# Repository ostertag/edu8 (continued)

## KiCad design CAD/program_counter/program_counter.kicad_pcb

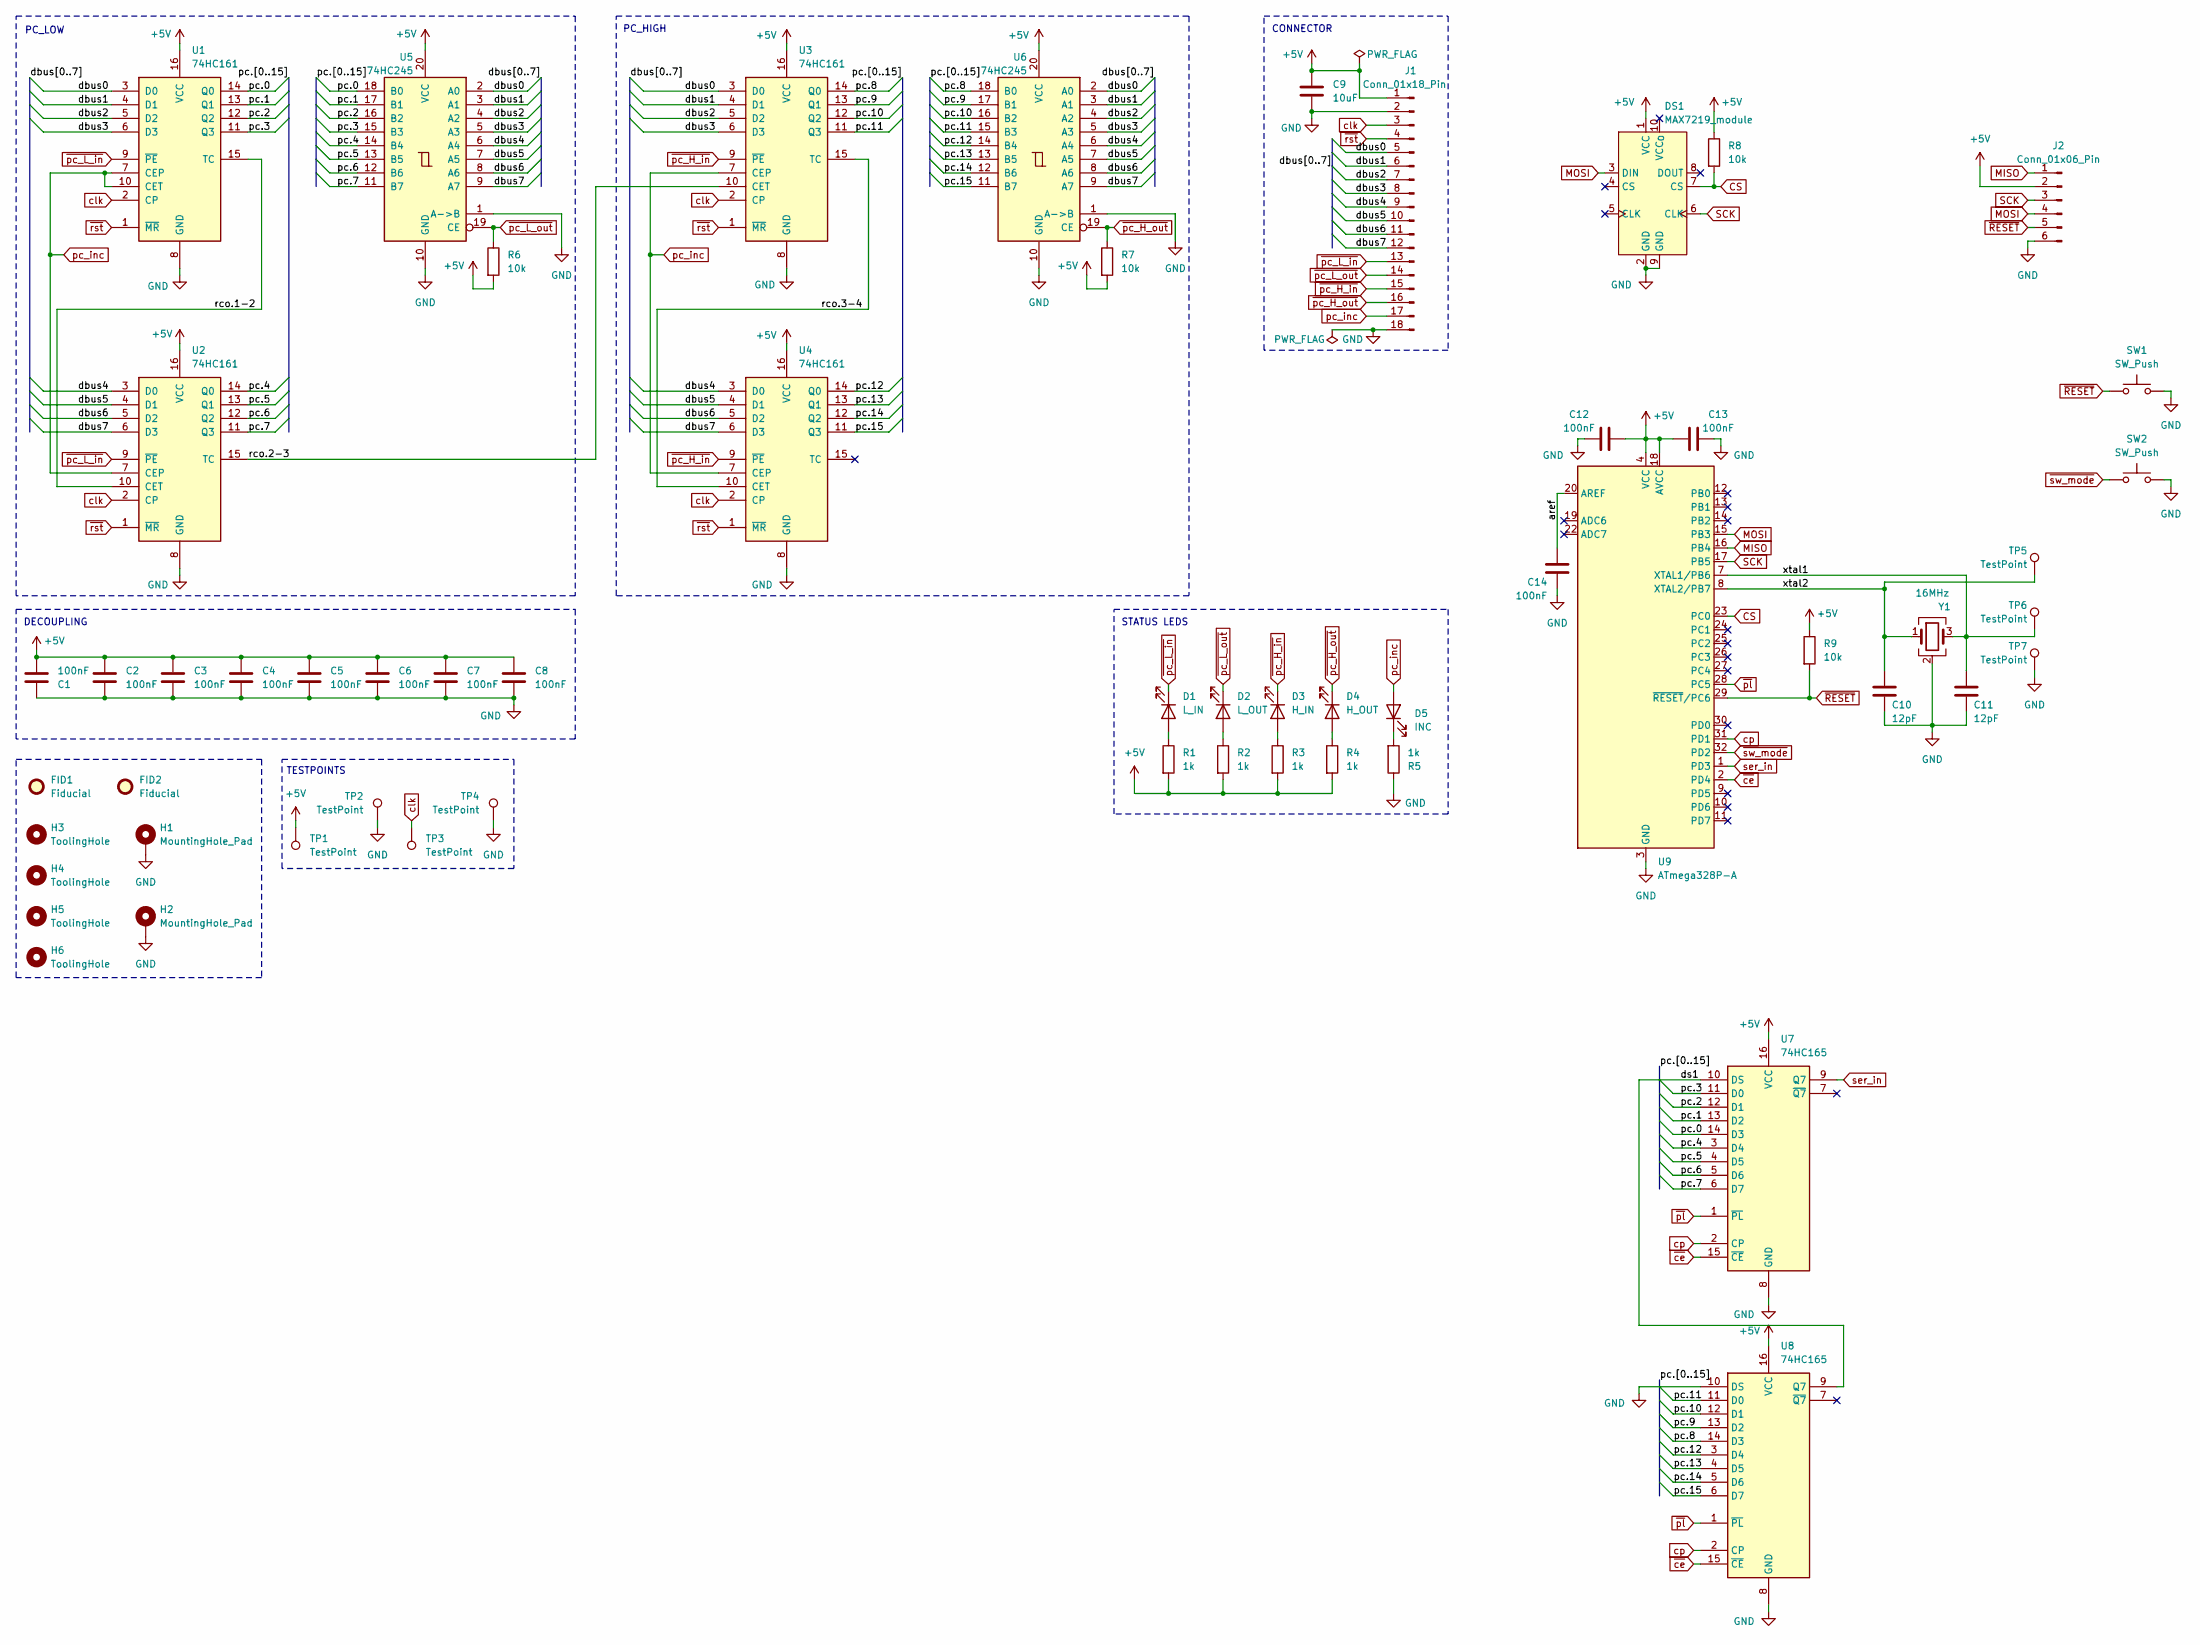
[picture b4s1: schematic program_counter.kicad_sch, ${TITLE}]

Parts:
C1, C2, C3, C4, C5, C6, C7, C8, C12, C13: 100nF; C_0805_2012Metric; LCSC C28233
C9: 10uF; C_0805_2012Metric; LCSC C15850
C10, C11: 12pF; C_0805_2012Metric; LCSC C1792
C14: 100nF; C_0805_2012Metric
D1: L_IN; LED_0805_2012Metric; LCSC C2297
D2: L_OUT; LED_0805_2012Metric; LCSC C2296
D3: H_IN; LED_0805_2012Metric; LCSC C2297
D4: H_OUT; LED_0805_2012Metric; LCSC C2296
D5: INC; LED_0805_2012Metric; LCSC C84256
DS1: MAX7219_module; MAX7219 7-segment module
FID1, FID2: Fiducial; Fiducial_0.5mm_Mask1mm
H1, H2: MountingHole_Pad; MountingHole_2.5mm_Pad_Via
H3, H4, H5, H6: ToolingHole; ToolingHole_1.152mm
J1: Conn_01x18_Pin; PinHeader_2x09_P2.54mm_Horizontal; LCSC C2894989
J2: Conn_01x06_Pin; PinHeader_2x03_P2.54mm_Vertical
R1, R2, R3, R4, R5: 1k; R_0805_2012Metric; LCSC C17513
R6, R7, R9: 10k; R_0805_2012Metric; LCSC C17414
R8: 10k; R_0805_2012Metric
SW1, SW2: SW_Push; SW_Push_1P1T_XKB_TS-1187A; LCSC C318884
TP1, TP2, TP3, TP4, TP5, TP6, TP7: TestPoint; TestPoint_THTPad_D1.0mm_Drill0.5mm
U1, U2, U3, U4: 74HC161; SO-16_3.9x9.9mm_P1.27mm; LCSC C6824
U5, U6: 74HC245; SOIC-20W_7.5x12.8mm_P1.27mm; LCSC C5625
U7, U8: 74HC165; SO-16_3.9x9.9mm_P1.27mm; LCSC C5613
U9: ATmega328P-A; TQFP-32_7x7mm_P0.8mm; LCSC C14877
Y1: 16MHz; Crystal_SMD_3225-4Pin_3.2x2.5mm; LCSC C13738

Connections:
+5V: C1.2, C2.1, C3.1, C4.1, C5.1, C6.1, C7.1, C8.1, C9.1, C12.2, C13.1, DS1.1 (VCC), J1.1, J2.2, R1.2, R2.2, R3.2, R4.2, R6.2, R7.2, R8.1, R9.1, TP1.1 (1_1), U1.16 (VCC), U2.16 (VCC), U3.16 (VCC), U4.16 (VCC), U5.20 (VCC), U6.20 (VCC), U7.16 (VCC), U8.16 (VCC), U9.4 (VCC), U9.6 (VCC), U9.18 (AVCC)
/aref: C14.1, U9.20 (AREF)
/dbus0: J1.5, U1.3 (D0), U3.3 (D0), U5.2 (A0), U6.2 (A0)
/dbus1: J1.6, U1.4 (D1), U3.4 (D1), U5.3 (A1), U6.3 (A1)
/dbus2: J1.7, U1.5 (D2), U3.5 (D2), U5.4 (A2), U6.4 (A2)
/dbus3: J1.8, U1.6 (D3), U3.6 (D3), U5.5 (A3), U6.5 (A3)
/dbus4: J1.9, U2.3 (D0), U4.3 (D0), U5.6 (A4), U6.6 (A4)
/dbus5: J1.10, U2.4 (D1), U4.4 (D1), U5.7 (A5), U6.7 (A5)
/dbus6: J1.11, U2.5 (D2), U4.5 (D2), U5.8 (A6), U6.8 (A6)
/dbus7: J1.12, U2.6 (D3), U4.6 (D3), U5.9 (A7), U6.9 (A7)
/ds1: U7.10 (DS), U8.9 (Q7)
/pc.0: U1.14 (Q0), U5.18 (B0), U7.14 (D3)
/pc.1: U1.13 (Q1), U5.17 (B1), U7.13 (D2)
/pc.2: U1.12 (Q2), U5.16 (B2), U7.12 (D1)
/pc.3: U1.11 (Q3), U5.15 (B3), U7.11 (D0)
/pc.4: U2.14 (Q0), U5.14 (B4), U7.3 (D4)
/pc.5: U2.13 (Q1), U5.13 (B5), U7.4 (D5)
/pc.6: U2.12 (Q2), U5.12 (B6), U7.5 (D6)
/pc.7: U2.11 (Q3), U5.11 (B7), U7.6 (D7)
/pc.8: U3.14 (Q0), U6.18 (B0), U8.14 (D3)
/pc.9: U3.13 (Q1), U6.17 (B1), U8.13 (D2)
/pc.10: U3.12 (Q2), U6.16 (B2), U8.12 (D1)
/pc.11: U3.11 (Q3), U6.15 (B3), U8.11 (D0)
/pc.12: U4.14 (Q0), U6.14 (B4), U8.3 (D4)
/pc.13: U4.13 (Q1), U6.13 (B5), U8.4 (D5)
/pc.14: U4.12 (Q2), U6.12 (B6), U8.5 (D6)
/pc.15: U4.11 (Q3), U6.11 (B7), U8.6 (D7)
/rco.1-2: U1.15 (TC), U2.10 (CET)
/rco.2-3: U2.15 (TC), U3.10 (CET)
/rco.3-4: U3.15 (TC), U4.10 (CET)
/xtal1: C11.1, TP6.1 (1_1), U9.7 (XTAL1/PB6), Y1.3
/xtal2: C10.1, TP5.1 (1_1), U9.8 (XTAL2/PB7), Y1.1
CS: DS1.7 (CS), R8.2, U9.23 (PC0)
GND: C1.1, C2.2, C3.2, C4.2, C5.2, C6.2, C7.2, C8.2, C9.2, C10.2, C11.2, C12.1, C13.2, C14.2, DS1.2 (GND), DS1.9 (GND), H1.1 (1_1), H2.1 (1_1), J1.2, J1.18, J2.6, R5.1, SW1.2, SW2.2, TP2.1 (1_1), TP4.1 (1_1), TP7.1 (1_1), U1.8 (GND), U2.8 (GND), U3.8 (GND), U4.8 (GND), U5.1 (A->B), U5.10 (GND), U6.1 (A->B), U6.10 (GND), U7.8 (GND), U8.8 (GND), U8.10 (DS), U9.3 (GND), U9.5 (GND), U9.21 (GND), Y1.2 (G), Y1.4 (G)
MISO: J2.1, U9.16 (PB4)
MOSI: DS1.3 (DIN), J2.4, U9.15 (PB3)
unnamed: D1.2 (A), R1.1
unnamed: D2.2 (A), R2.1
unnamed: D3.2 (A), R3.1
unnamed: D4.2 (A), R4.1
unnamed: D5.1 (K), R5.2
SCK: DS1.6 (CLK), J2.3, U9.17 (PB5)
clk: J1.3, TP3.1 (1_1), U1.2 (CP), U2.2 (CP), U3.2 (CP), U4.2 (CP)
cp: U7.2 (CP), U8.2 (CP), U9.31 (PD1)
pc_inc: D5.2 (A), J1.17, U1.7 (CEP), U1.10 (CET), U2.7 (CEP), U3.7 (CEP), U4.7 (CEP)
ser_in: U7.9 (Q7), U9.1 (PD3)
~RESET: J2.5, R9.2, SW1.1, U9.29 (~RESET/PC6)
~ce: U7.15 (~CE), U8.15 (~CE), U9.2 (PD4)
~pc_H_in: D3.1 (K), J1.15, U3.9 (~PE), U4.9 (~PE)
~pc_H_out: D4.1 (K), J1.16, R7.1, U6.19 (CE)
~pc_L_in: D1.1 (K), J1.13, U1.9 (~PE), U2.9 (~PE)
~pc_L_out: D2.1 (K), J1.14, R6.1, U5.19 (CE)
~pl: U7.1 (~PL), U8.1 (~PL), U9.28 (PC5)
~rst: J1.4, U1.1 (~MR), U2.1 (~MR), U3.1 (~MR), U4.1 (~MR)
~sw_mode: SW2.1, U9.32 (PD2)

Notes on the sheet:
PC_HIGH
PC_LOW
STATUS LEDS
DECOUPLING
CONNECTOR
TESTPOINTS

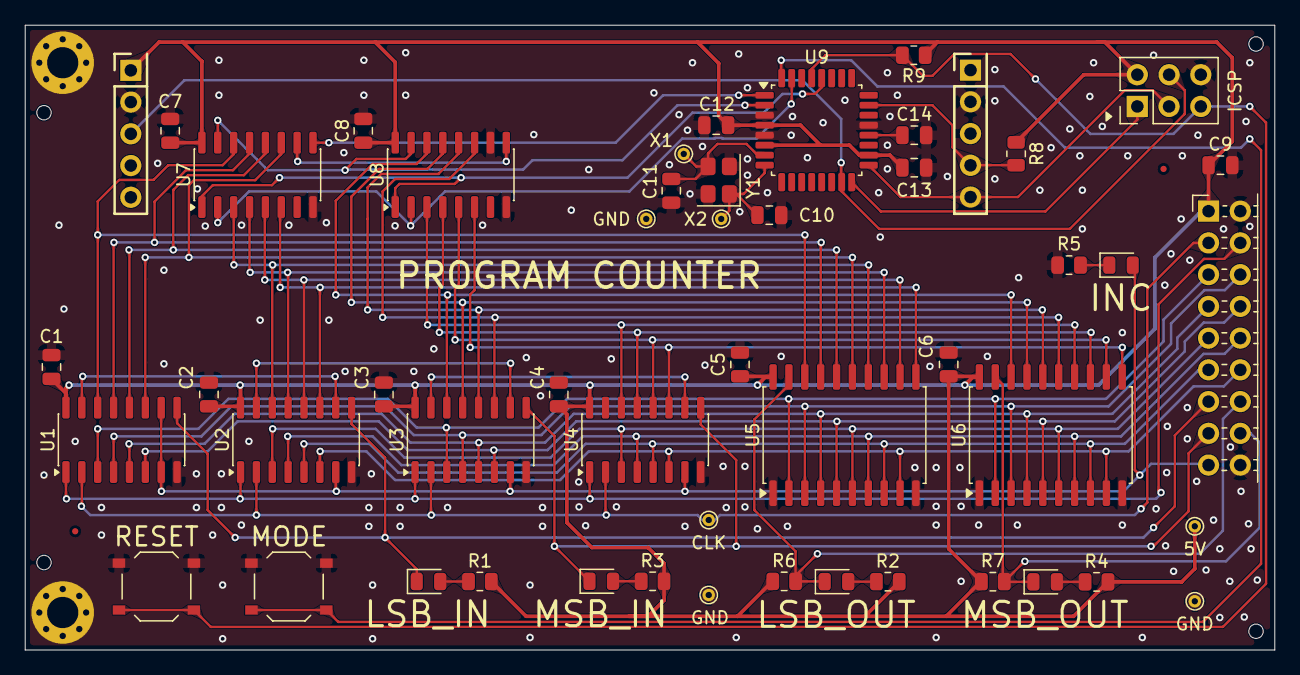
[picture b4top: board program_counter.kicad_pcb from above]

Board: 2 copper layers, 100.0 x 50.0 mm, 59 parts (1 on the bottom side), 55 nets.

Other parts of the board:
Ref**: Val**; by-nc-sa.eu

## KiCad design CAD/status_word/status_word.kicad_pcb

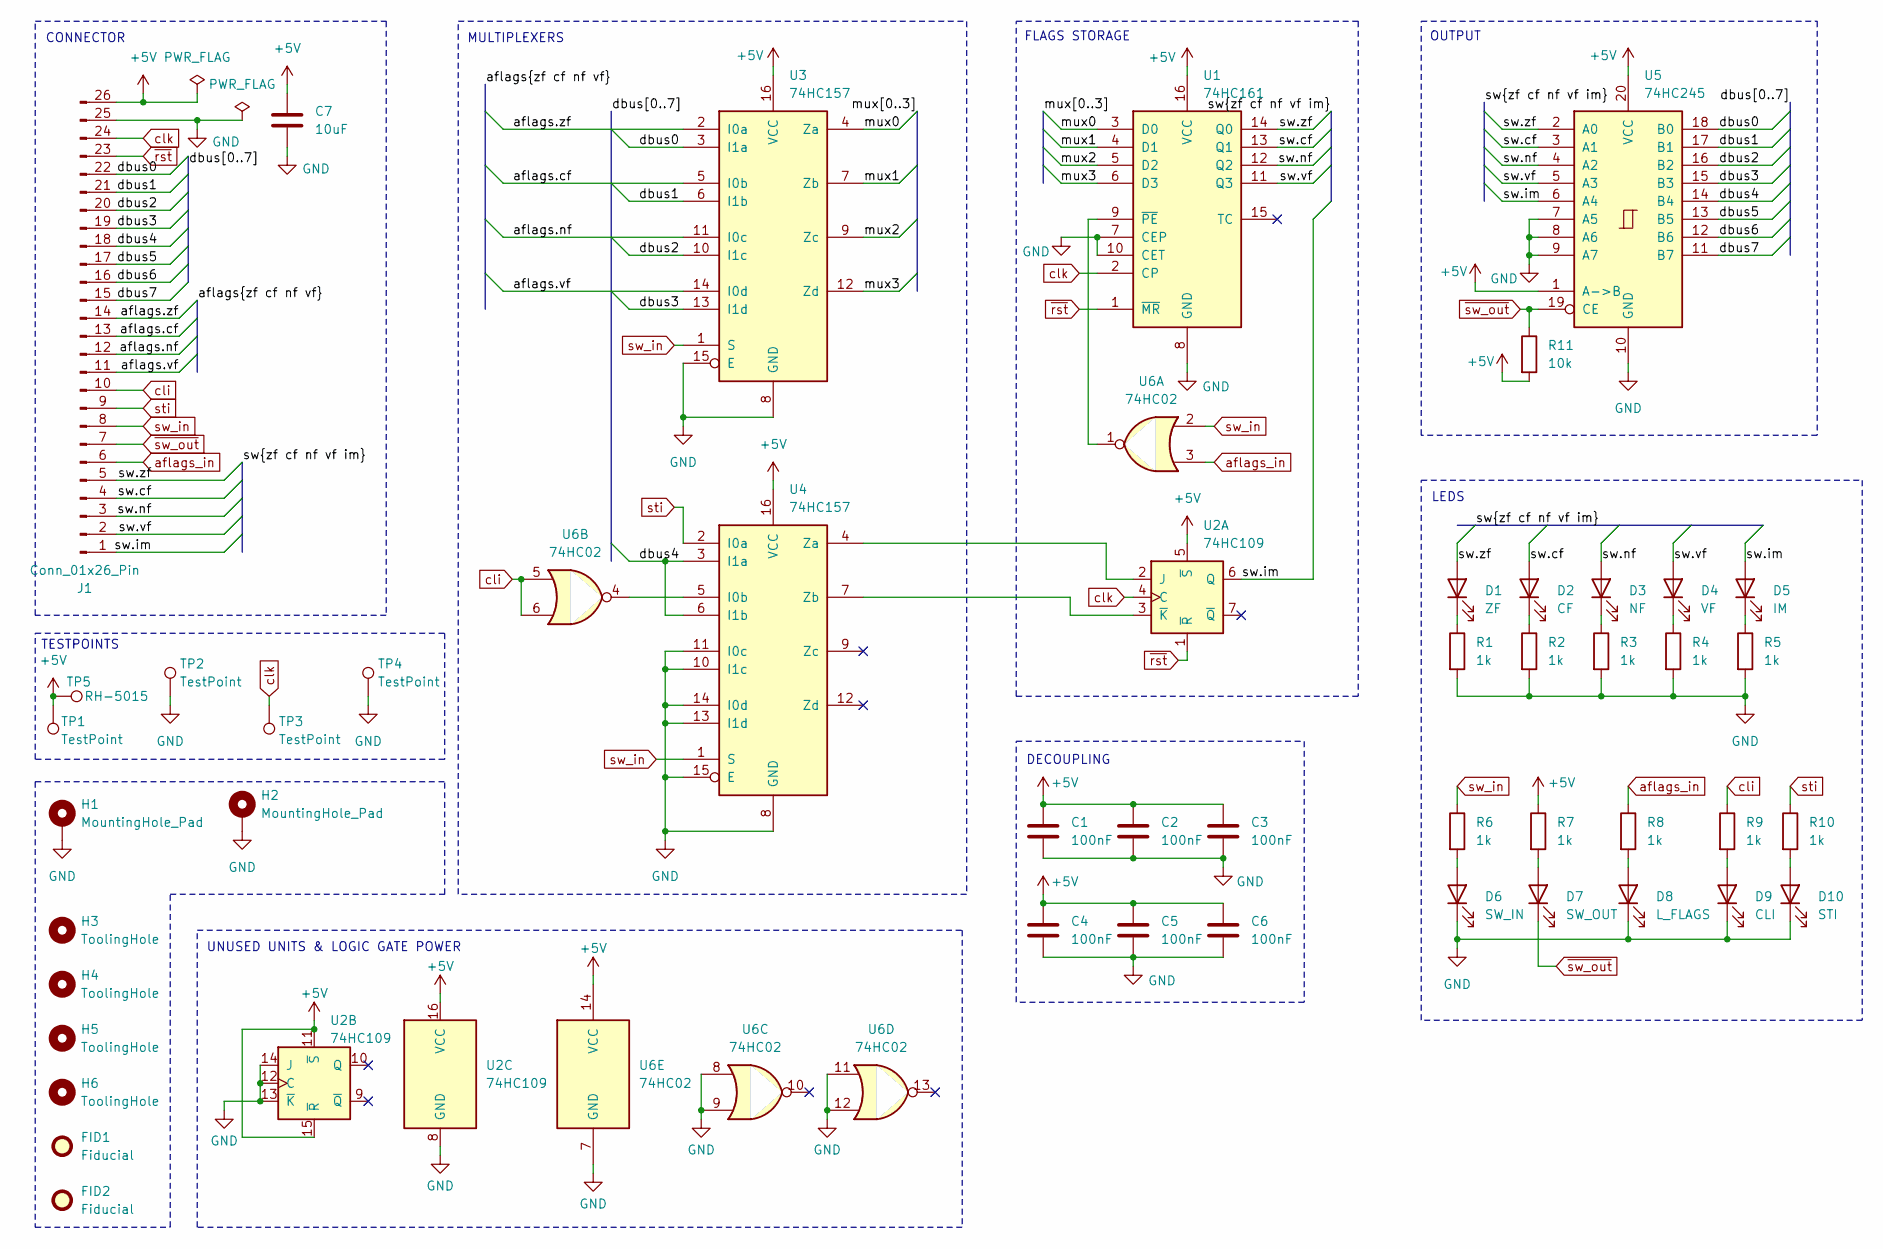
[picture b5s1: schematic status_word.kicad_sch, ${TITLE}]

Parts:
C1, C2, C3, C4, C5, C6: 100nF; C_0805_2012Metric; LCSC C28233
C7: 10uF; C_0805_2012Metric; LCSC C15850
D1: ZF; LED_0805_2012Metric; LCSC C84256
D2: CF; LED_0805_2012Metric; LCSC C84256
D3: NF; LED_0805_2012Metric; LCSC C84256
D4: VF; LED_0805_2012Metric; LCSC C84256
D5: IM; LED_0805_2012Metric; LCSC C84256
D6: SW_IN; LED_0805_2012Metric; LCSC C2297
D7: SW_OUT; LED_0805_2012Metric; LCSC C2296
D8: L_FLAGS; LED_0805_2012Metric; LCSC C2297
D9: CLI; LED_0805_2012Metric; LCSC C2296
D10: STI; LED_0805_2012Metric; LCSC C2296
FID1, FID2: Fiducial; Fiducial_0.5mm_Mask1mm
H1, H2: MountingHole_Pad; MountingHole_2.5mm_Pad_Via
H3, H4, H5, H6: ToolingHole; ToolingHole_1.152mm
J1: Conn_01x26_Pin; PinHeader_2x13_P2.54mm_Horizontal; LCSC C2894993
R1, R2, R3, R4, R5, R6, R7, R8, R9, R10: 1k; R_0805_2012Metric; LCSC C17513
R11: 10k; R_0805_2012Metric; LCSC C17414
TP1, TP2, TP3, TP4: TestPoint; TestPoint_THTPad_D1.0mm_Drill0.5mm
TP5: RH-5015; TestPoint_Keystone_5015_Micro_Mini; LCSC C5199798
U1: 74HC161; SO-16_3.9x9.9mm_P1.27mm; LCSC C6824
U2: 74HC109; SO-16_3.9x9.9mm_P1.27mm; LCSC C2860677
U3, U4: 74HC157; SO-16_3.9x9.9mm_P1.27mm; LCSC C6823
U5: 74HC245; SOIC-20W_7.5x12.8mm_P1.27mm; LCSC C5625
U6: 74HC02; SO-14_3.9x8.65mm_P1.27mm; LCSC C350559

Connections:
+5V: C1.1, C2.1, C3.1, C4.1, C5.1, C6.1, C7.1, J1.26, R7.1, R11.2, TP1.1 (1_1), TP5.1 (1_1), U1.16 (VCC), U2.5 (~S), U2.11 (~S), U2.15 (~R), U2.16 (VCC), U3.16 (VCC), U4.16 (VCC), U5.1 (A->B), U5.20 (VCC), U6.14 (VCC)
/aflags.cf: J1.13, U3.5 (I0b)
/aflags.nf: J1.12, U3.11 (I0c)
/aflags.vf: J1.11, U3.14 (I0d)
/aflags.zf: J1.14, U3.2 (I0a)
/dbus0: J1.22, U3.3 (I1a), U5.18 (B0)
/dbus1: J1.21, U3.6 (I1b), U5.17 (B1)
/dbus2: J1.20, U3.10 (I1c), U5.16 (B2)
/dbus3: J1.19, U3.13 (I1d), U5.15 (B3)
/dbus4: J1.18, U4.3 (I1a), U4.6 (I1b), U5.14 (B4)
/dbus5: J1.17, U5.13 (B5)
/dbus6: J1.16, U5.12 (B6)
/dbus7: J1.15, U5.11 (B7)
/mux0: U1.3 (D0), U3.4 (Za)
/mux1: U1.4 (D1), U3.7 (Zb)
/mux2: U1.5 (D2), U3.9 (Zc)
/mux3: U1.6 (D3), U3.12 (Zd)
/sw.cf: D2.2 (A), J1.4, U1.13 (Q1), U5.3 (A1)
/sw.im: D5.2 (A), J1.1, U2.6 (Q), U5.6 (A4)
/sw.nf: D3.2 (A), J1.3, U1.12 (Q2), U5.4 (A2)
/sw.vf: D4.2 (A), J1.2, U1.11 (Q3), U5.5 (A3)
/sw.zf: D1.2 (A), J1.5, U1.14 (Q0), U5.2 (A0)
GND: C1.2, C2.2, C3.2, C4.2, C5.2, C6.2, C7.2, D6.1 (K), D8.1 (K), D9.1 (K), D10.1 (K), H1.1 (1_1), H2.1 (1_1), J1.25, R1.2, R2.2, R3.2, R4.2, R5.2, TP2.1 (1_1), TP4.1 (1_1), U1.7 (CEP), U1.8 (GND), U1.10 (CET), U2.8 (GND), U2.12 (C), U2.13 (~K), U2.14 (J), U3.8 (GND), U3.15 (E), U4.8 (GND), U4.10 (I1c), U4.11 (I0c), U4.13 (I1d), U4.14 (I0d), U4.15 (E), U5.7 (A5), U5.8 (A6), U5.9 (A7), U5.10 (GND), U6.7 (GND), U6.8, U6.9, U6.11, U6.12
unnamed: D1.1 (K), R1.1
unnamed: D2.1 (K), R2.1
unnamed: D3.1 (K), R3.1
unnamed: D4.1 (K), R4.1
unnamed: D5.1 (K), R5.1
unnamed: D6.2 (A), R6.2
unnamed: D7.2 (A), R7.2
unnamed: D8.2 (A), R8.2
unnamed: D9.2 (A), R9.2
unnamed: D10.2 (A), R10.2
unnamed: U1.9 (~PE), U6.1
unnamed: U2.2 (J), U4.4 (Za)
unnamed: U2.3 (~K), U4.7 (Zb)
unnamed: U4.5 (I0b), U6.4
aflags_in: J1.6, R8.1, U6.3
cli: J1.10, R9.1, U6.5, U6.6
clk: J1.24, TP3.1 (1_1), U1.2 (CP), U2.4 (C)
sti: J1.9, R10.1, U4.2 (I0a)
sw_in: J1.8, R6.1, U3.1 (S), U4.1 (S), U6.2
~rst: J1.23, U1.1 (~MR), U2.1 (~R)
~sw_out: D7.1 (K), J1.7, R11.1, U5.19 (CE)

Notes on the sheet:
MULTIPLEXERS
DECOUPLING
TESTPOINTS
OUTPUT
FLAGS STORAGE
CONNECTOR
LEDS
UNUSED UNITS & LOGIC GATE POWER

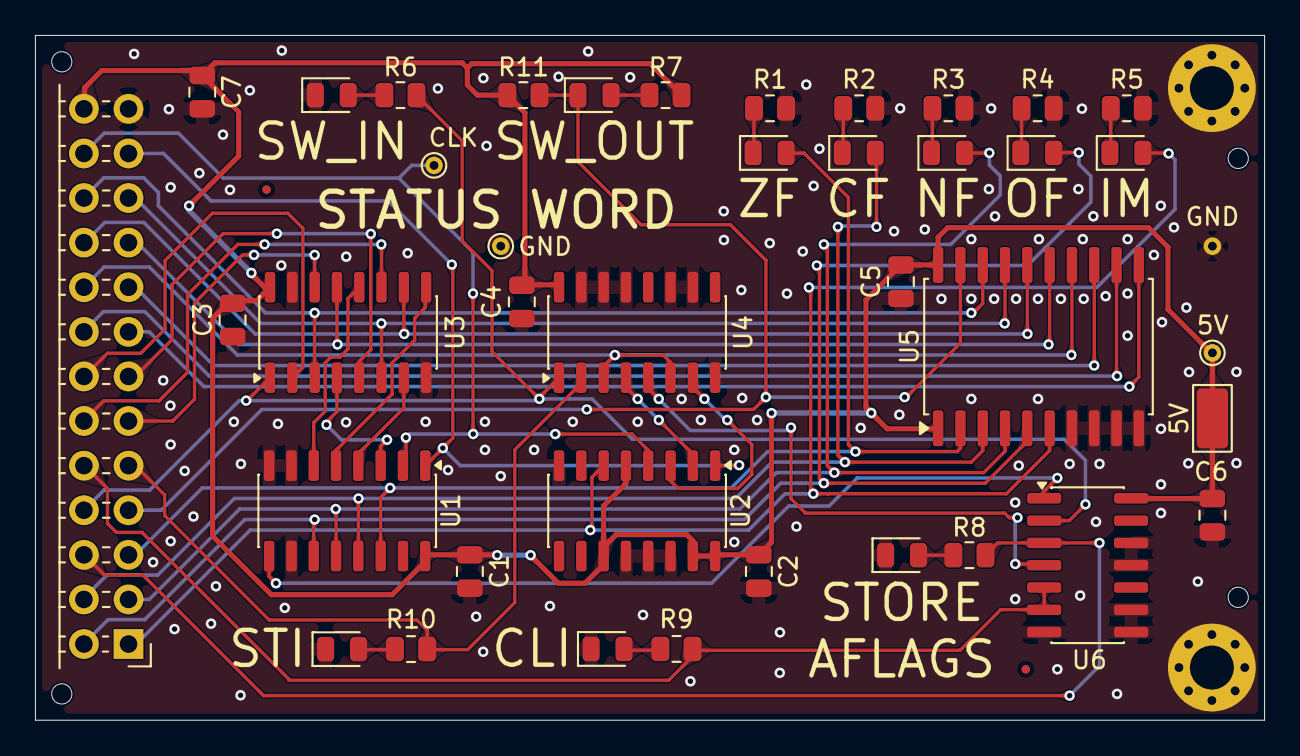
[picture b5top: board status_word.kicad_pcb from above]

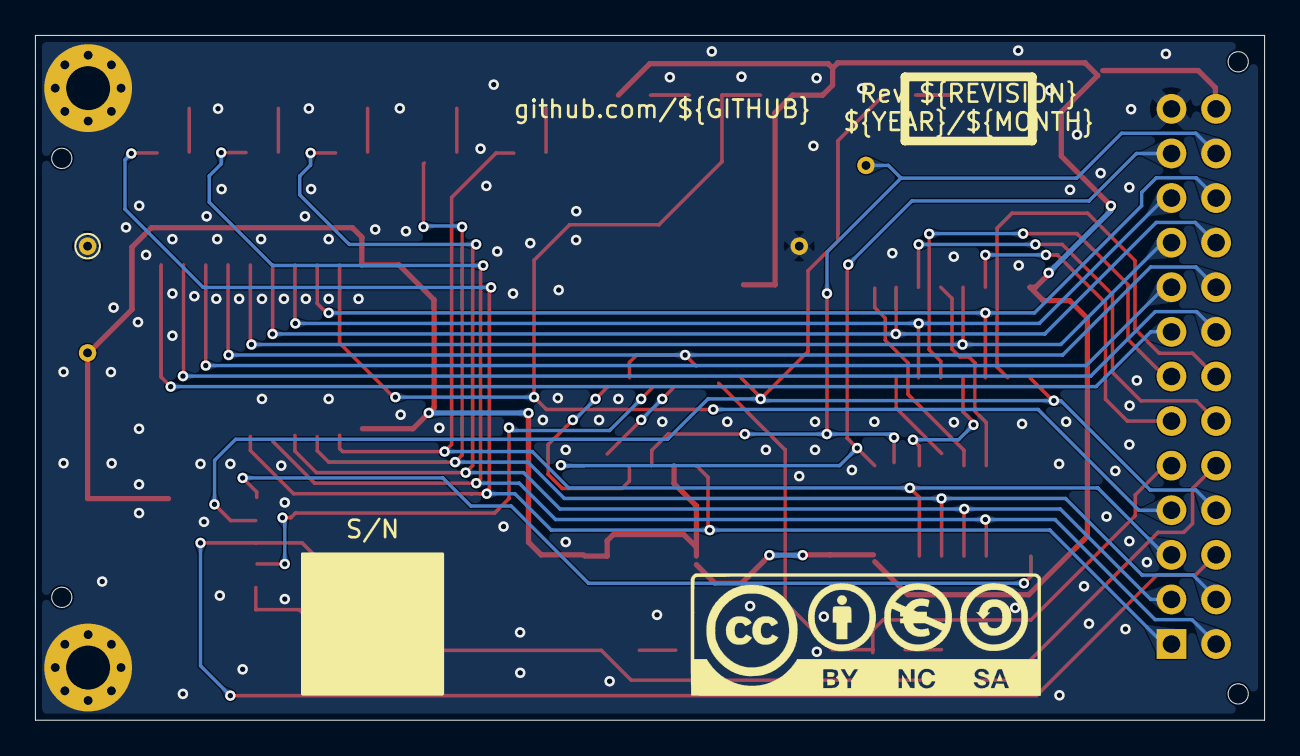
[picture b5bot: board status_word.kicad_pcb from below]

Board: 2 copper layers, 70.0 x 39.0 mm, 49 parts (2 on the bottom side), 44 nets.

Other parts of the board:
Ref**: Val**; by-nc-sa.eu

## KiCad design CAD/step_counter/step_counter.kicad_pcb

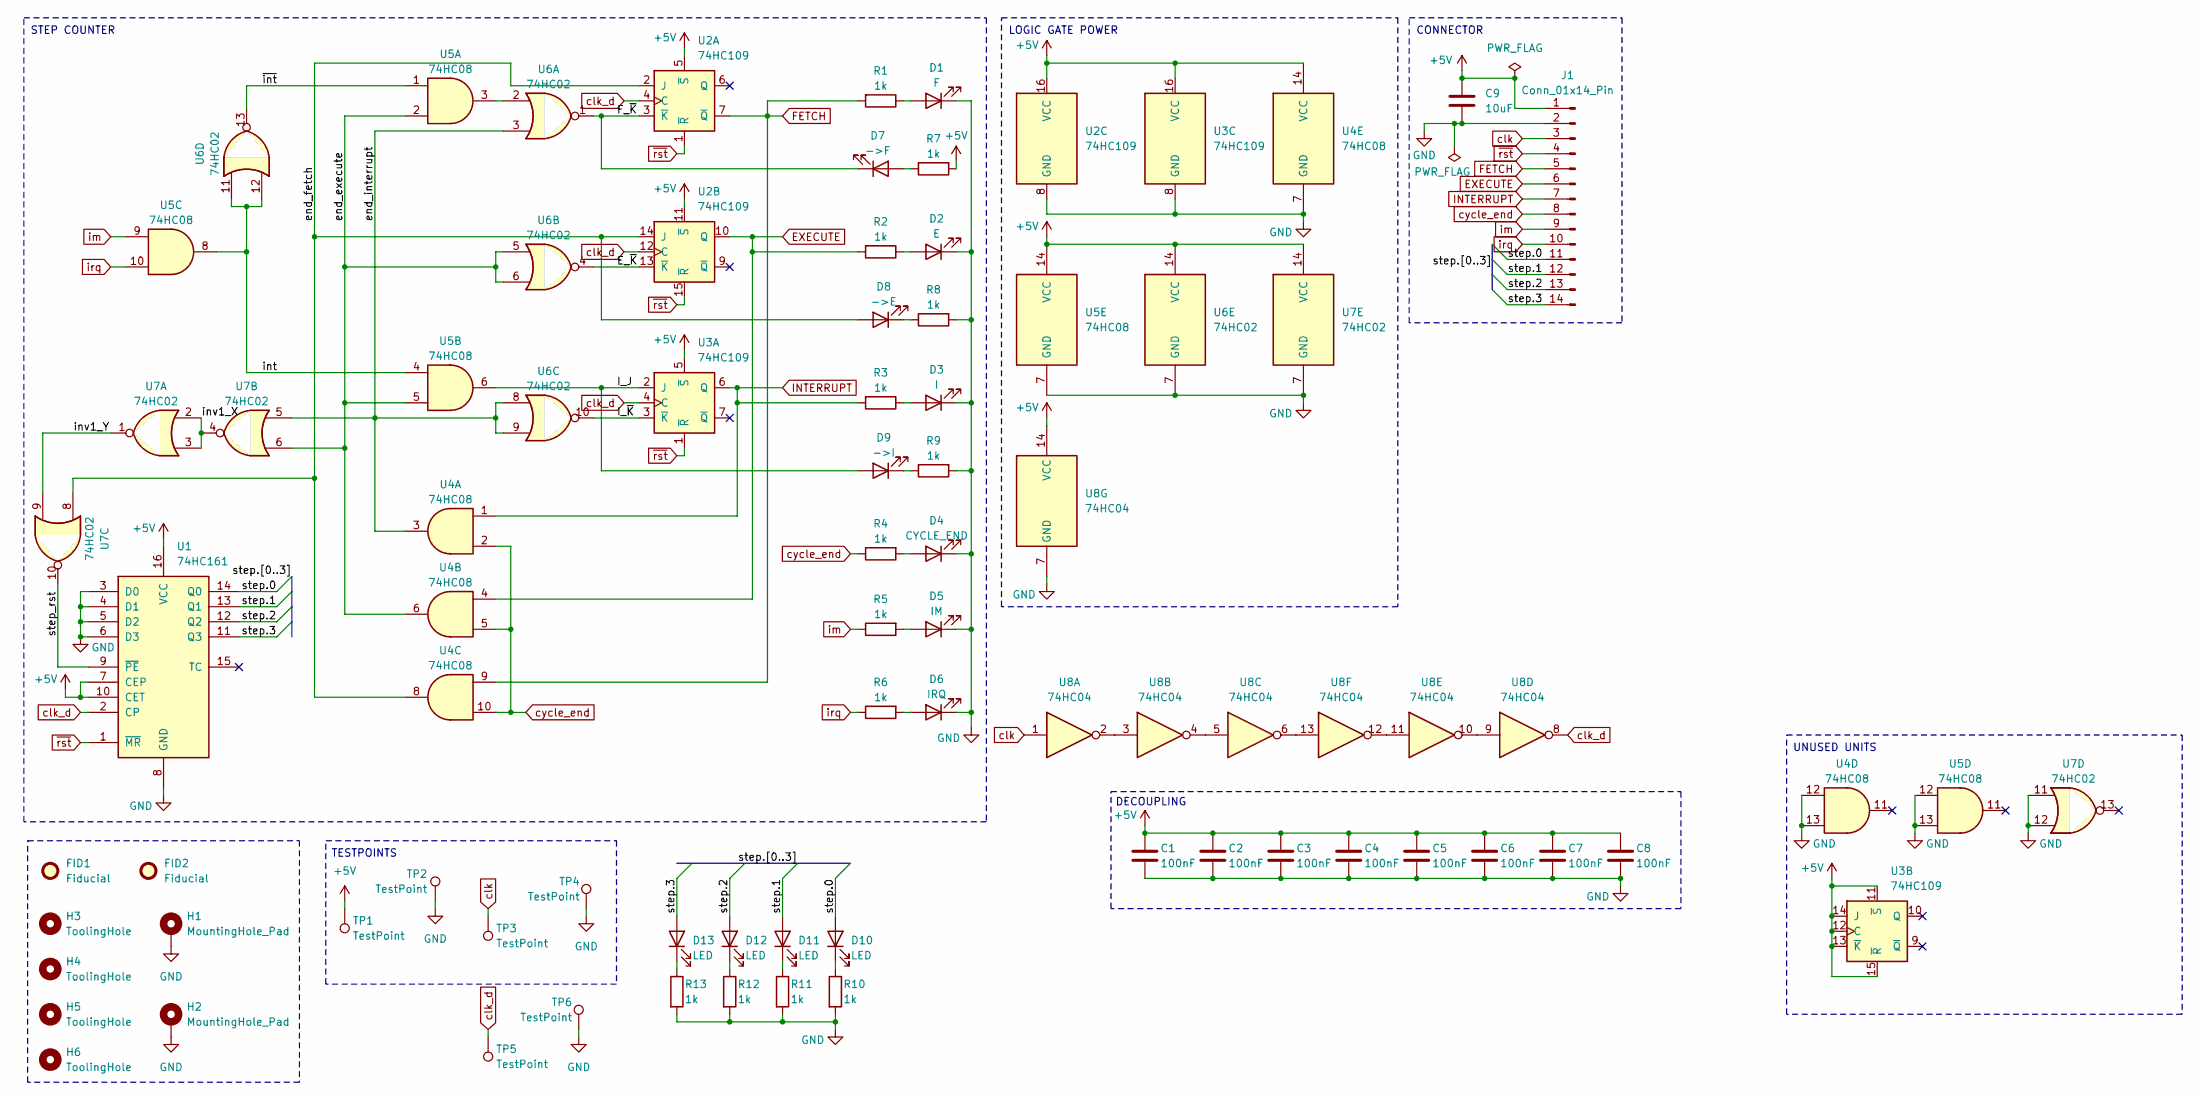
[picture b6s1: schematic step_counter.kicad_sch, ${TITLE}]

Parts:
C1, C2, C3, C4, C5, C6, C7, C8: 100nF; C_0805_2012Metric; LCSC C28233
C9: 10uF; C_0805_2012Metric; LCSC C15850
D1: F; LED_0805_2012Metric; LCSC C2297
D2: E; LED_0805_2012Metric; LCSC C84256
D3: I; LED_0805_2012Metric; LCSC C2296
D4: CYCLE_END; LED_0805_2012Metric; LCSC C2296
D5: IM; LED_0805_2012Metric; LCSC C2296
D6: IRQ; LED_0805_2012Metric; LCSC C84256
D7: ->F; LED_0805_2012Metric; LCSC C2297
D8: ->E; LED_0805_2012Metric
D9: ->I; LED_0805_2012Metric; LCSC C2296
D10, D11, D12, D13: LED; LED_0805_2012Metric; LCSC C2297
FID1, FID2: Fiducial; Fiducial_0.5mm_Mask1mm
H1, H2: MountingHole_Pad; MountingHole_2.5mm_Pad_Via
H3, H4, H5, H6: ToolingHole; ToolingHole_1.152mm
J1: Conn_01x14_Pin; PinHeader_2x07_P2.54mm_Horizontal; LCSC C492435
R1, R2, R3, R4, R5, R6, R7, R8, R9, R10, R11, R12, R13: 1k; R_0805_2012Metric; LCSC C17513
TP1, TP2, TP3, TP4, TP5, TP6: TestPoint; TestPoint_THTPad_D1.0mm_Drill0.5mm
U1: 74HC161; SO-16_3.9x9.9mm_P1.27mm; LCSC C6824
U2, U3: 74HC109; SO-16_3.9x9.9mm_P1.27mm; LCSC C2860677
U4, U5: 74HC08; SO-14_3.9x8.65mm_P1.27mm; LCSC C5593
U6, U7: 74HC02; SO-14_3.9x8.65mm_P1.27mm; LCSC C350559
U8: 74HC04; SO-14_3.9x8.65mm_P1.27mm; LCSC C5590

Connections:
+5V: C1.1, C2.1, C3.1, C4.1, C5.1, C6.1, C7.1, C8.1, C9.1, J1.1, R7.2, TP1.1 (1_1), U1.7 (CEP), U1.10 (CET), U1.16 (VCC), U2.5 (~S), U2.11 (~S), U2.16 (VCC), U3.5 (~S), U3.11 (~S), U3.12 (C), U3.13 (~K), U3.14 (J), U3.15 (~R), U3.16 (VCC), U4.14 (VCC), U5.14 (VCC), U6.14 (VCC), U7.14 (VCC), U8.14 (VCC)
/E_~K: U2.13 (~K), U6.4
/F_~K: D7.1 (K), U2.3 (~K), U6.1
/I_J: D9.2 (A), U3.2 (J), U5.6
/I_~K: U3.3 (~K), U6.10
/end_execute: U4.6, U5.2, U5.5, U6.5, U6.6, U7.6
/end_fetch: D8.2 (A), U2.2 (J), U2.14 (J), U4.8, U7.8
/end_interrupt: U4.3, U6.3, U6.8, U6.9, U7.5
/int: U5.4, U5.8, U6.11, U6.12
/inv1_X: U7.2, U7.3, U7.4
/inv1_Y: U7.1, U7.9
/step.0: D10.2 (A), J1.11, U1.14 (Q0)
/step.1: D11.2 (A), J1.12, U1.13 (Q1)
/step.2: D12.2 (A), J1.13, U1.12 (Q2)
/step.3: D13.2 (A), J1.14, U1.11 (Q3)
/step_rst: U1.9 (~PE), U7.10
/~int: U5.1, U6.13
EXECUTE: J1.6, R2.2, U2.10 (Q), U4.4
FETCH: J1.5, R1.2, U2.7 (~Q), U4.9
GND: C1.2, C2.2, C3.2, C4.2, C5.2, C6.2, C7.2, C8.2, C9.2, D1.1 (K), D2.1 (K), D3.1 (K), D4.1 (K), D5.1 (K), D6.1 (K), H1.1 (1_1), H2.1 (1_1), J1.2, R8.2, R9.2, R10.2, R11.2, R12.2, R13.2, TP2.1 (1_1), TP4.1 (1_1), TP6.1 (1_1), U1.3 (D0), U1.4 (D1), U1.5 (D2), U1.6 (D3), U1.8 (GND), U2.8 (GND), U3.8 (GND), U4.7 (GND), U4.12, U4.13, U5.7 (GND), U5.12, U5.13, U6.7 (GND), U7.7 (GND), U7.11, U7.12, U8.7 (GND)
INTERRUPT: J1.7, R3.2, U3.6 (Q), U4.1
unnamed: D1.2 (A), R1.1
unnamed: D2.2 (A), R2.1
unnamed: D3.2 (A), R3.1
unnamed: D4.2 (A), R4.2
unnamed: D5.2 (A), R5.2
unnamed: D6.2 (A), R6.2
unnamed: D7.2 (A), R7.1
unnamed: D8.1 (K), R8.1
unnamed: D9.1 (K), R9.1
unnamed: D10.1 (K), R10.1
unnamed: D11.1 (K), R11.1
unnamed: D12.1 (K), R12.1
unnamed: D13.1 (K), R13.1
unnamed: U5.3, U6.2
unnamed: U8.2, U8.3
unnamed: U8.4, U8.5
unnamed: U8.9, U8.10
unnamed: U8.11, U8.12
unnamed: U8.6, U8.13
clk: J1.3, TP3.1 (1_1), U8.1
clk_d: TP5.1 (1_1), U1.2 (CP), U2.4 (C), U2.12 (C), U3.4 (C), U8.8
cycle_end: J1.8, R4.1, U4.2, U4.5, U4.10
im: J1.9, R5.1, U5.9
irq: J1.10, R6.1, U5.10
~rst: J1.4, U1.1 (~MR), U2.1 (~R), U2.15 (~R), U3.1 (~R)

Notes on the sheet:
CONNECTOR
STEP COUNTER
DECOUPLING
TESTPOINTS
UNUSED UNITS
LOGIC GATE POWER

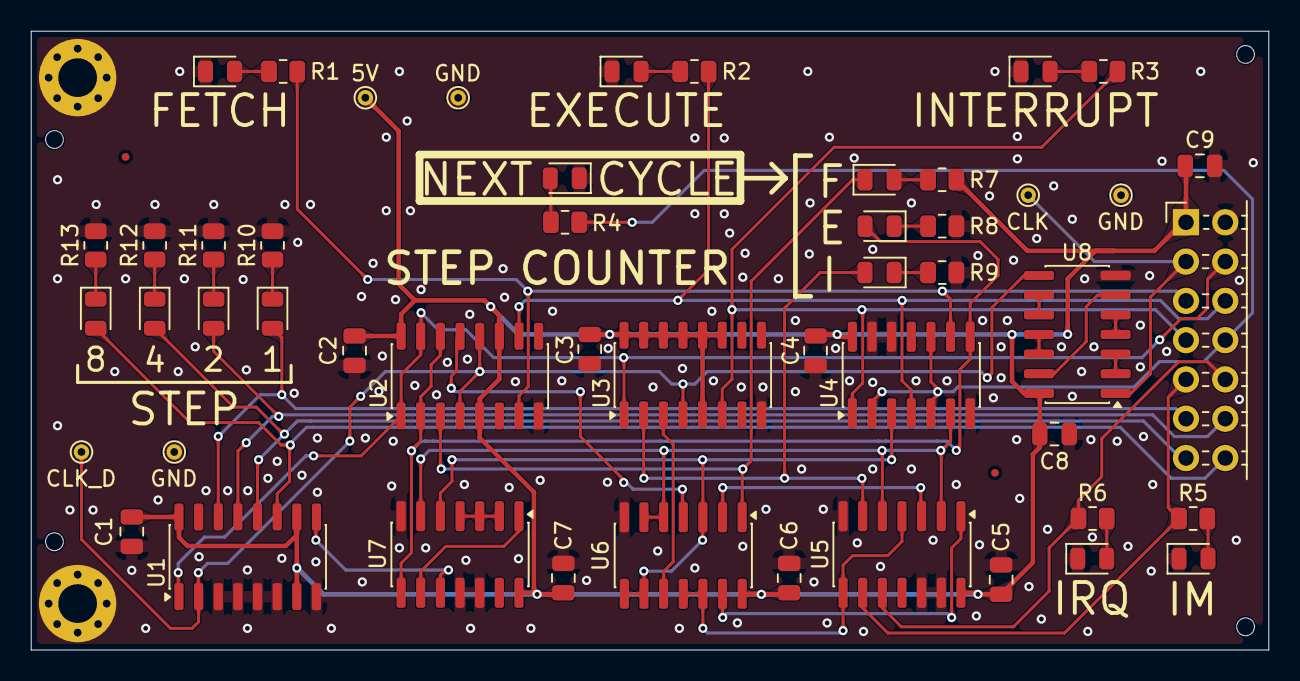
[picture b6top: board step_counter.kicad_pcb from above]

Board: 2 copper layers, 80.0 x 40.0 mm, 59 parts (1 on the bottom side), 46 nets.

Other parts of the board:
Ref**: Val**; by-nc-sa.eu
